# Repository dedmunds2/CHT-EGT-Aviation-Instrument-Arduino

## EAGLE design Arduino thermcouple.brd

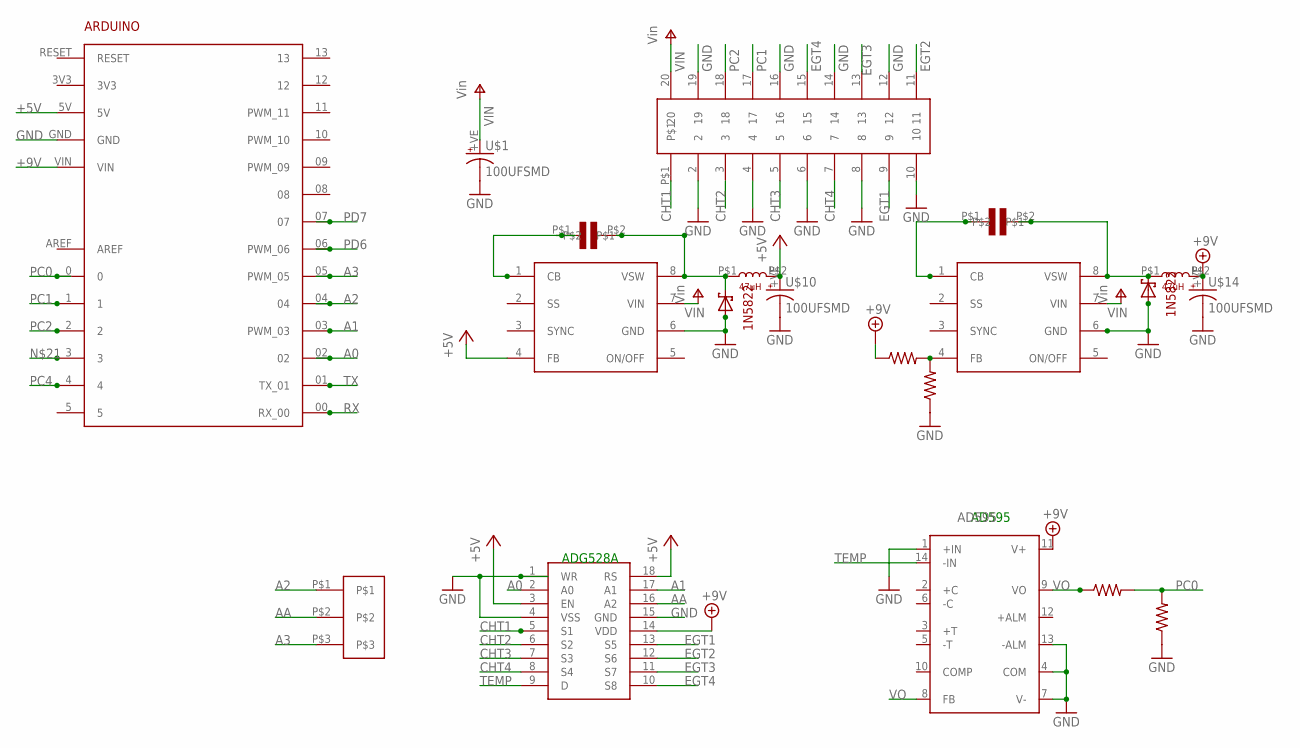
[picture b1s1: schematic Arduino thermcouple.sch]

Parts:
": ADG528A; DIL18
ARDUINO2: ARDUINO
IC2: AD595; DIL14
R5, R6: 10K; 0.3RESISTOR
U$1, U$10, U$14: 100UFSMD
U$2, U$4: 1N5822
U$3, U$6: LM2672; DIL08
U$5, U$7: 01CAP
U$8: 20PIN0.1INCH
U$9, U$13: 47uH; 47UHSMD
U$15: 1K5; 0.3RESISTOR
U$16: 10K; 0.3RESISTOR
U$17: 3PINHEADER

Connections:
+5V: ".3 (EN), ".18 (RS), ARDUINO2.5V, U$3.4 (FB), U$9.P$2 (2), U$10.+VE (+)
+9V: ".14 (VDD), ARDUINO2.VIN, IC2.11 (V+), U$13.P$2 (2), U$14.+VE (+), U$16.P$1 (1)
A0: ".2 (A0), ARDUINO2.02
A1: ".17 (A1), ARDUINO2.03 (PWM_03)
A2: ARDUINO2.04, U$17.P$1
A3: ARDUINO2.05 (PWM_05), U$17.P$3
AA: ".16 (A2), U$17.P$2
CHT1: ".5 (S1), U$8.P$1
CHT2: ".6 (S2), U$8.3
CHT3: ".7 (S3), U$8.5
CHT4: ".8 (S4), U$8.7
EGT1: ".13 (S5), U$8.9
EGT2: ".12 (S6), U$8.11
EGT3: ".11 (S7), U$8.13
EGT4: ".10 (S8), U$8.15
GND: ".1 (WR), ".4 (VSS), ".15 (GND), ARDUINO2.GND, IC2.1 (+IN), IC2.4 (COM), IC2.7 (V-), IC2.13 (-ALM), R6.P$1 (1), U$1.-VE (-), U$2.A, U$3.6 (GND), U$4.A, U$6.6 (GND), U$8.2, U$8.4, U$8.6, U$8.8, U$8.10, U$8.12, U$8.14, U$8.16, U$8.19, U$10.-VE (-), U$14.-VE (-), U$15.P$1 (1)
unnamed: U$6.1 (CB), U$7.P$1
unnamed: U$3.1 (CB), U$5.P$1
unnamed: U$2.K (C), U$3.8 (VSW), U$5.P$2, U$9.P$1 (1)
unnamed: U$6.4 (FB), U$15.P$2 (2), U$16.P$2 (2)
unnamed: U$4.K (C), U$6.8 (VSW), U$7.P$2, U$13.P$1 (1)
PC0: ARDUINO2.0, R5.P$2 (2), R6.P$2 (2)
PC1: ARDUINO2.1, U$8.17
PC2: ARDUINO2.2, U$8.18
PC4: ARDUINO2.4
PD6: ARDUINO2.06 (PWM_06)
PD7: ARDUINO2.07
RX: ARDUINO2.00 (RX_00)
TEMP: ".9 (D), IC2.14 (-IN)
TX: ARDUINO2.01 (TX_01)
VIN: U$1.+VE (+), U$3.7 (VIN), U$6.7 (VIN), U$8.20
VO: IC2.8 (FB), IC2.9 (VO), R5.P$1 (1)

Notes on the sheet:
ADG528A
AD595

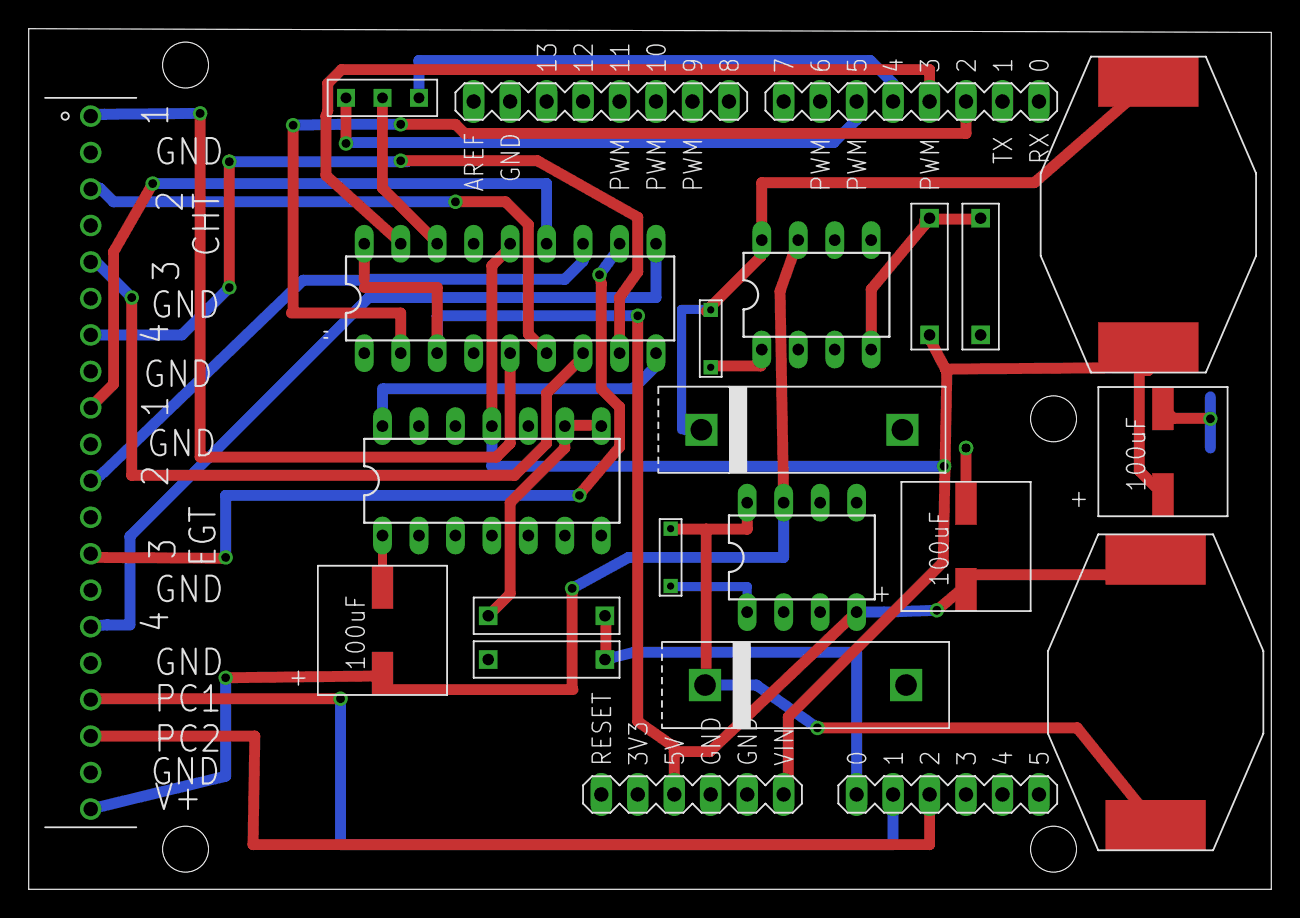
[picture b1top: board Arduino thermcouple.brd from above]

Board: 2 copper layers, 86.5 x 59.9 mm, 20 parts (0 on the bottom side), 27 nets.

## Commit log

2015-07-14 First commit
    CHT and EGT aviation instrumentation
2015-07-14 Eagle files added
2015-09-01 fix to multiplexer address space
